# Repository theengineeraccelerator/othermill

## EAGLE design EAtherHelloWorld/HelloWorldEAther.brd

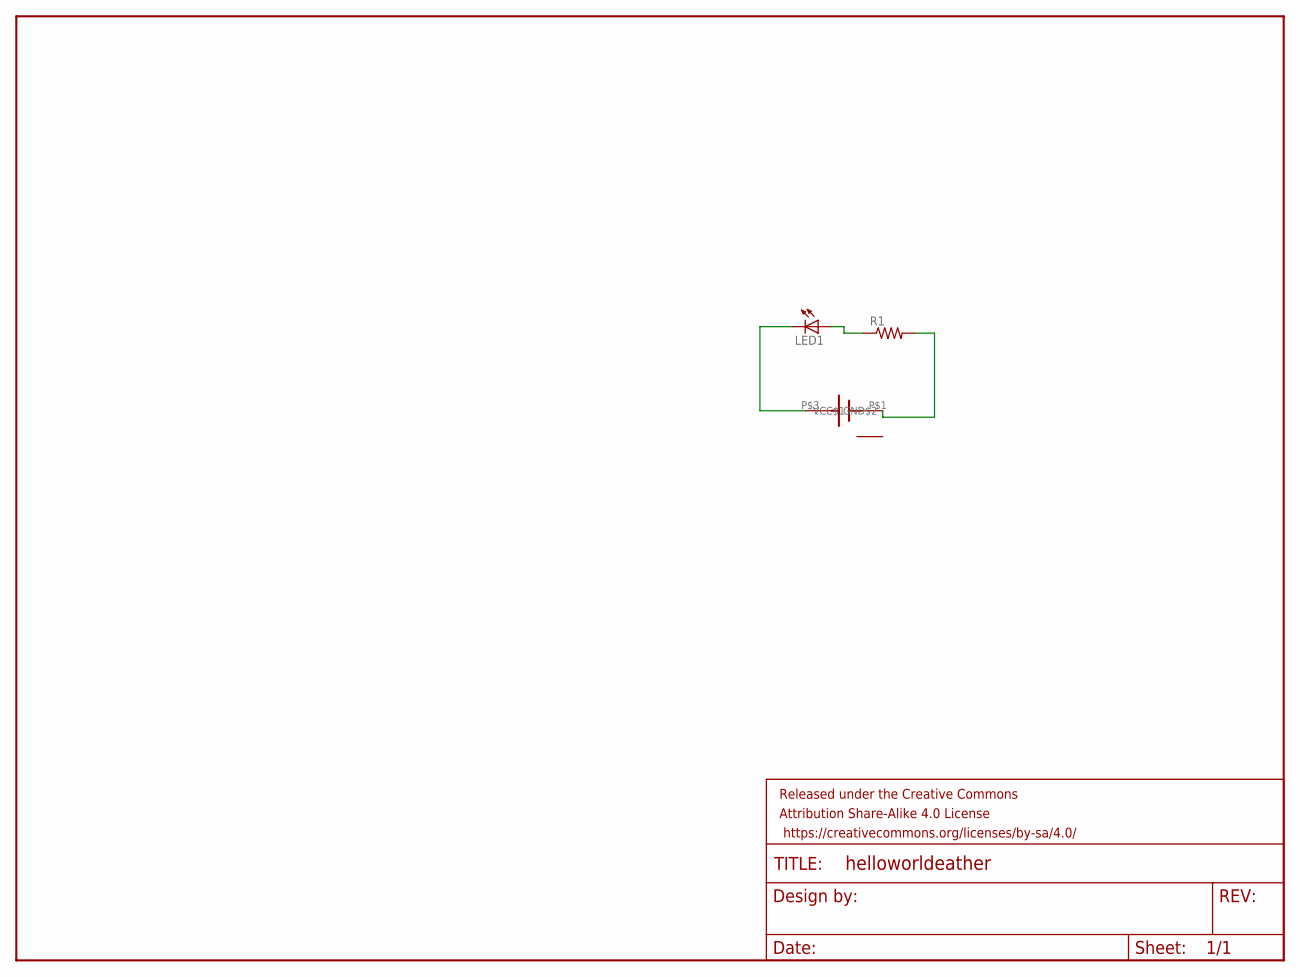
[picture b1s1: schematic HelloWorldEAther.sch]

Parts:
FRAME1: FRAME-LETTER; CREATIVE_COMMONS
LED1: LED_E; LED_1206
R1: R-US_R0805; R0805
U$1: CR1025

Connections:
BAT: R1.2, U$1.P$1 (VCC$1)
LED: LED1.C, U$1.P$3 (GND$2)
R: LED1.A, R1.1
VCC: U$1.P$2 (VCC)

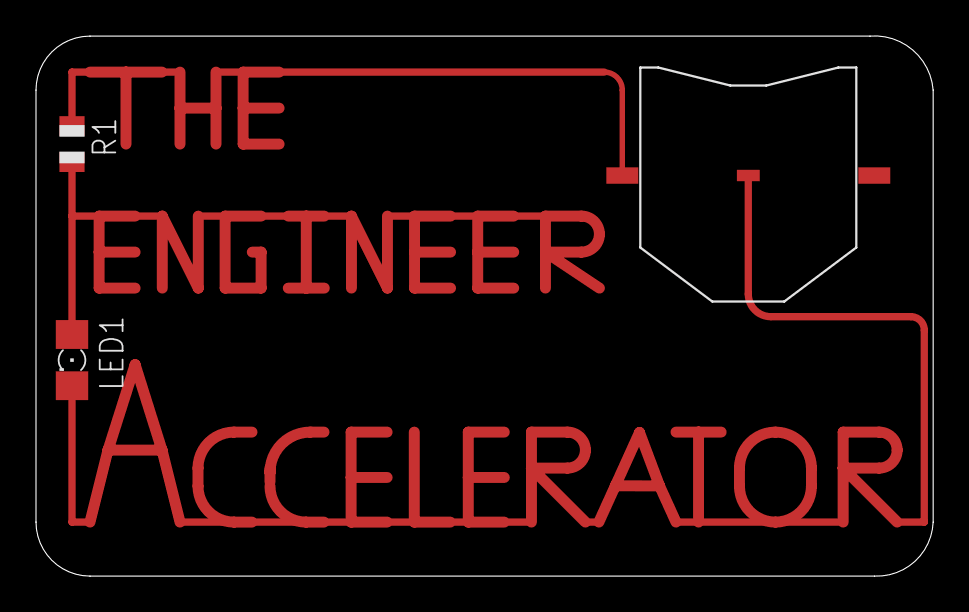
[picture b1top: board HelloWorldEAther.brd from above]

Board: 2 copper layers, 49.8 x 30.0 mm, 4 parts (0 on the bottom side), 3 nets.

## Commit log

2017-03-11 Add Othermill Hello World
2017-07-08 Added EA tutorial board

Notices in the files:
parts and their libraries:
SparkFun-Aesthetics: Licensing: Creative Commons ShareAlike 4.0 International - https://creativecommons.org/licenses/by-sa/4.0
SparkFun-Aesthetics: Released under the Creative Commons Attribution Share-Alike 4.0 License
SparkFun-Aesthetics: https://creativecommons.org/licenses/by-sa/4.0
